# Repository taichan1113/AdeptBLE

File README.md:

# Excuse

This is alpha version of Ploopy Adept BLE modification.

All necessary files are here but they are still messy.

Document may not reach your satisfaction.

## electronics

Designed by KiCAD and produted by [JLCPCB](https://jlcpcb.com/)

Basically you need XIAO nRF52840 board, PMW3610 optical sensor, omron D2LS-21 mouse switch, 6-pin slide switch and battery.

Other parts are set as below.

## firmware

Here includes uf2 file built by zmk.

You can find the code [here](https://github.com/taichan1113/mouse-test/tree/main).

## housing

I designed like you only need bottom modified housing additionally.

Note that put the battery wire not to interfere both top and bottom housings.

And you need to cut battery switch so as not to interfere the desk surface.

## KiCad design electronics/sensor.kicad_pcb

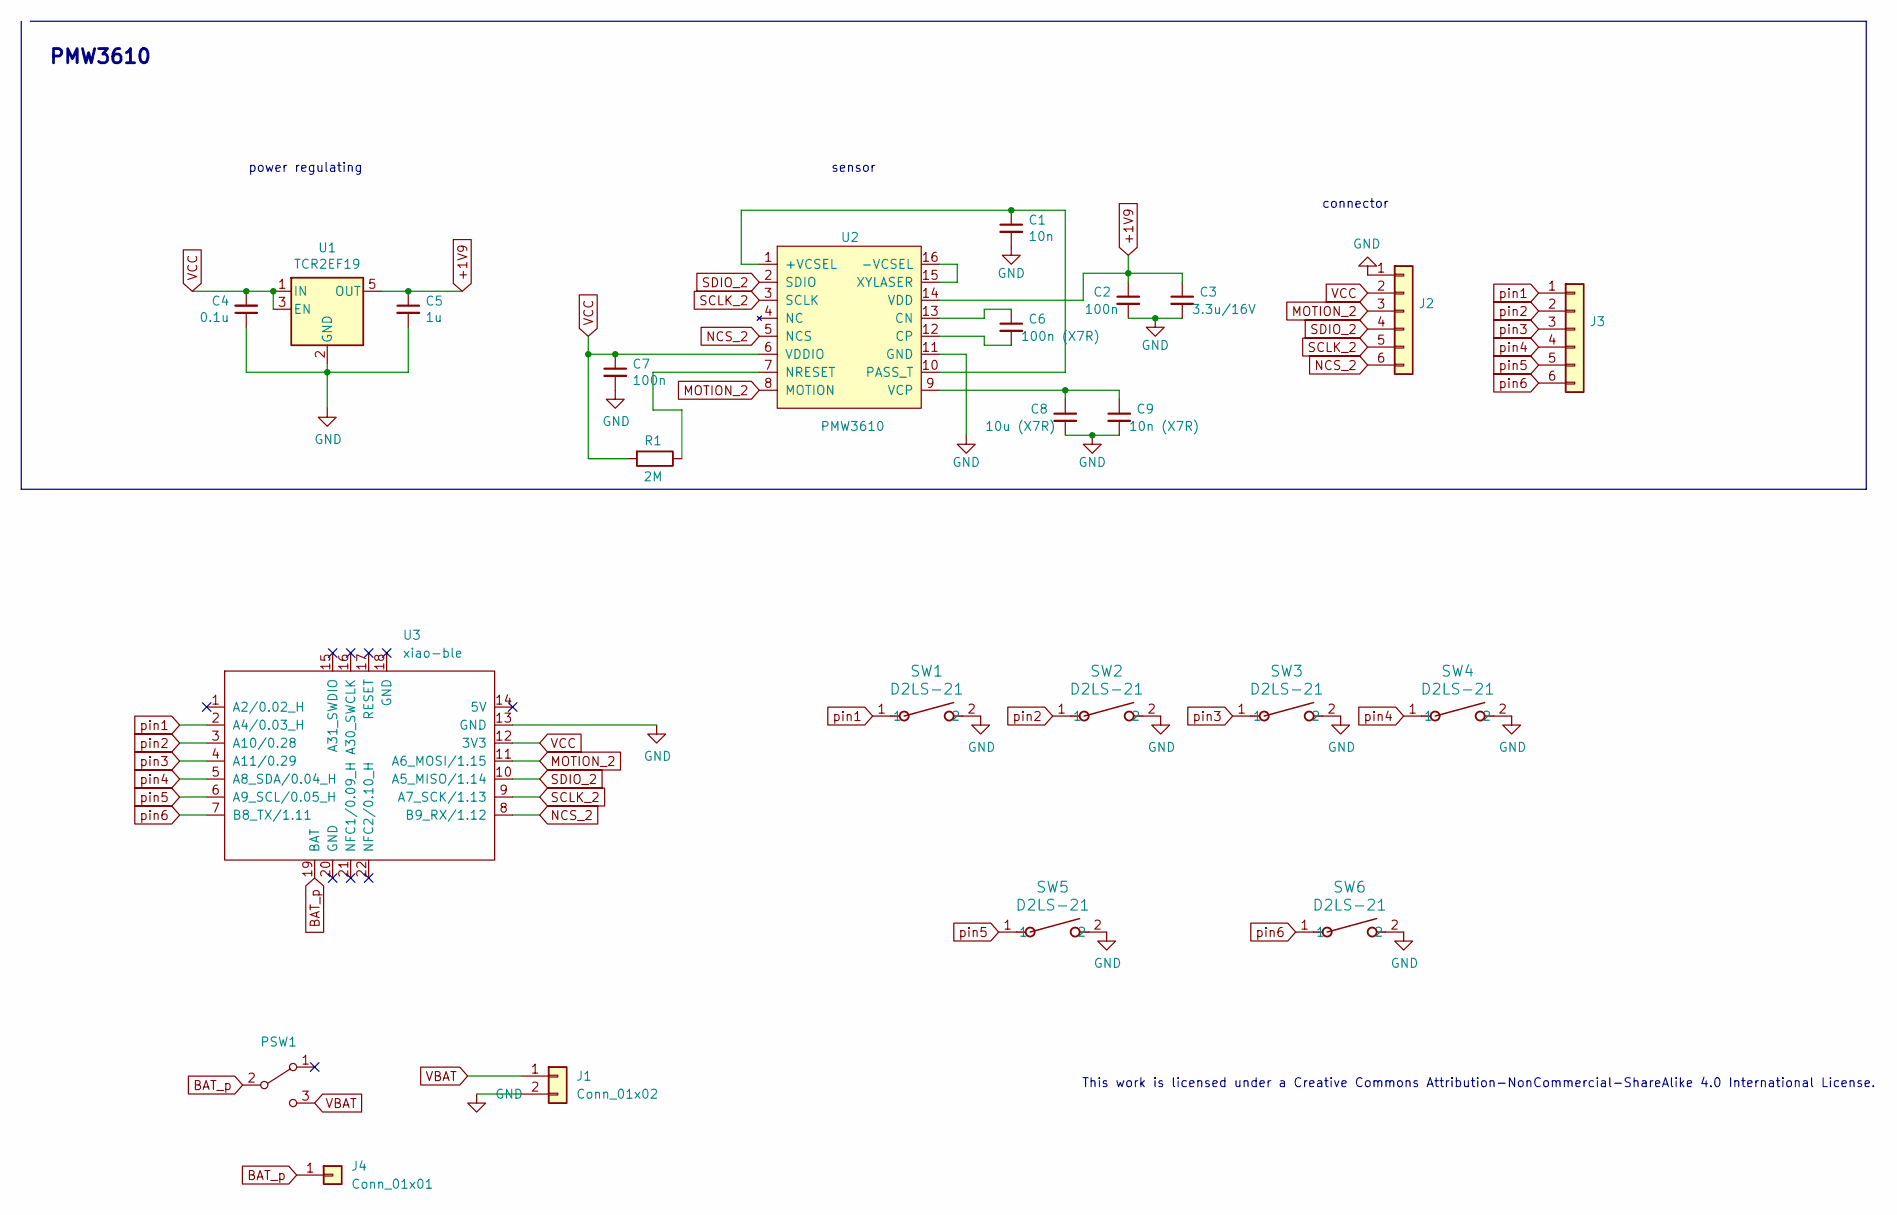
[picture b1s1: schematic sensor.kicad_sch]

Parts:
C1: 10n; C_0603_1608Metric; LCSC C19666
C2, C7: 100n; C_0603_1608Metric; LCSC C19666
C3: 3.3u/16V; C_0603_1608Metric; LCSC C19666
C4: 0.1u; C_0603_1608Metric; LCSC C14663
C5: 1u; C_0603_1608Metric; LCSC C15849
C6: 100n (X7R); C_0603_1608Metric; LCSC C19666
C8: 10u (X7R); C_0603_1608Metric; LCSC C19666
C9: 10n (X7R); C_0603_1608Metric; LCSC C19666
J1: Conn_01x02; Battery_2pin
J2, J3: Conn_01x06; PinHeader_1x06_P2.54mm_Vertical
J4: Conn_01x01; PinHeader_1x01_P2.54mm_Vertical
PSW1: SW_SPDT; TGSW_MSK-12D19
R1: 2M; R_0603_1608Metric
SW1, SW2, SW3, SW4, SW5, SW6: D2LS-21; SW_D2LS-11_2_OMR
U1: TCR2EF19; SOT-23-5; LCSC C146366
U2: PMW3610
U3: xiao-ble; xiao-ble-tht

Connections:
+1V9: C2.1, C3.1, C5.1, U1.5 (OUT), U2.14 (VDD)
BAT_p: J4.1, PSW1.2 (B), U3.19 (BAT)
GND: C1.2, C2.2, C3.2, C4.1, C5.2, C7.2, C8.2, C9.2, J1.2, J2.1, SW1.2, SW2.2, SW3.2, SW4.2, SW5.2, SW6.2, U1.2 (GND), U2.11 (GND), U3.13 (GND)
MOTION_2: J2.3, U2.8 (MOTION), U3.11 (A6_MOSI/1.15)
NCS_2: J2.6, U2.5 (NCS), U3.8 (B9_RX/1.12)
unnamed: C1.1, U2.1 (+VCSEL), U2.10 (PASS_T)
unnamed: U2.15 (XYLASER), U2.16 (-VCSEL)
unnamed: C6.1, U2.13 (CN)
unnamed: C6.2, U2.12 (CP)
unnamed: R1.1, U2.7 (NRESET)
unnamed: C8.1, C9.1, U2.9 (VCP)
SCLK_2: J2.5, U2.3 (SCLK), U3.9 (A7_SCK/1.13)
SDIO_2: J2.4, U2.2 (SDIO), U3.10 (A5_MISO/1.14)
VBAT: J1.1, PSW1.3 (C)
VCC: C4.2, C7.1, J2.2, R1.2, U1.1 (IN), U1.3 (EN), U2.6 (VDDIO), U3.12 (3V3)
pin1: J3.1, SW1.1, U3.2 (A4/0.03_H)
pin2: J3.2, SW2.1, U3.3 (A10/0.28)
pin3: J3.3, SW3.1, U3.4 (A11/0.29)
pin4: J3.4, SW4.1, U3.5 (A8_SDA/0.04_H)
pin5: J3.5, SW5.1, U3.6 (A9_SCL/0.05_H)
pin6: J3.6, SW6.1, U3.7 (B8_TX/1.11)

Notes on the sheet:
This work is licensed under a Creative Commons Attribution-NonCommercial-ShareAlike 4.0 International License.
sensor
PMW3610
power regulating
connector

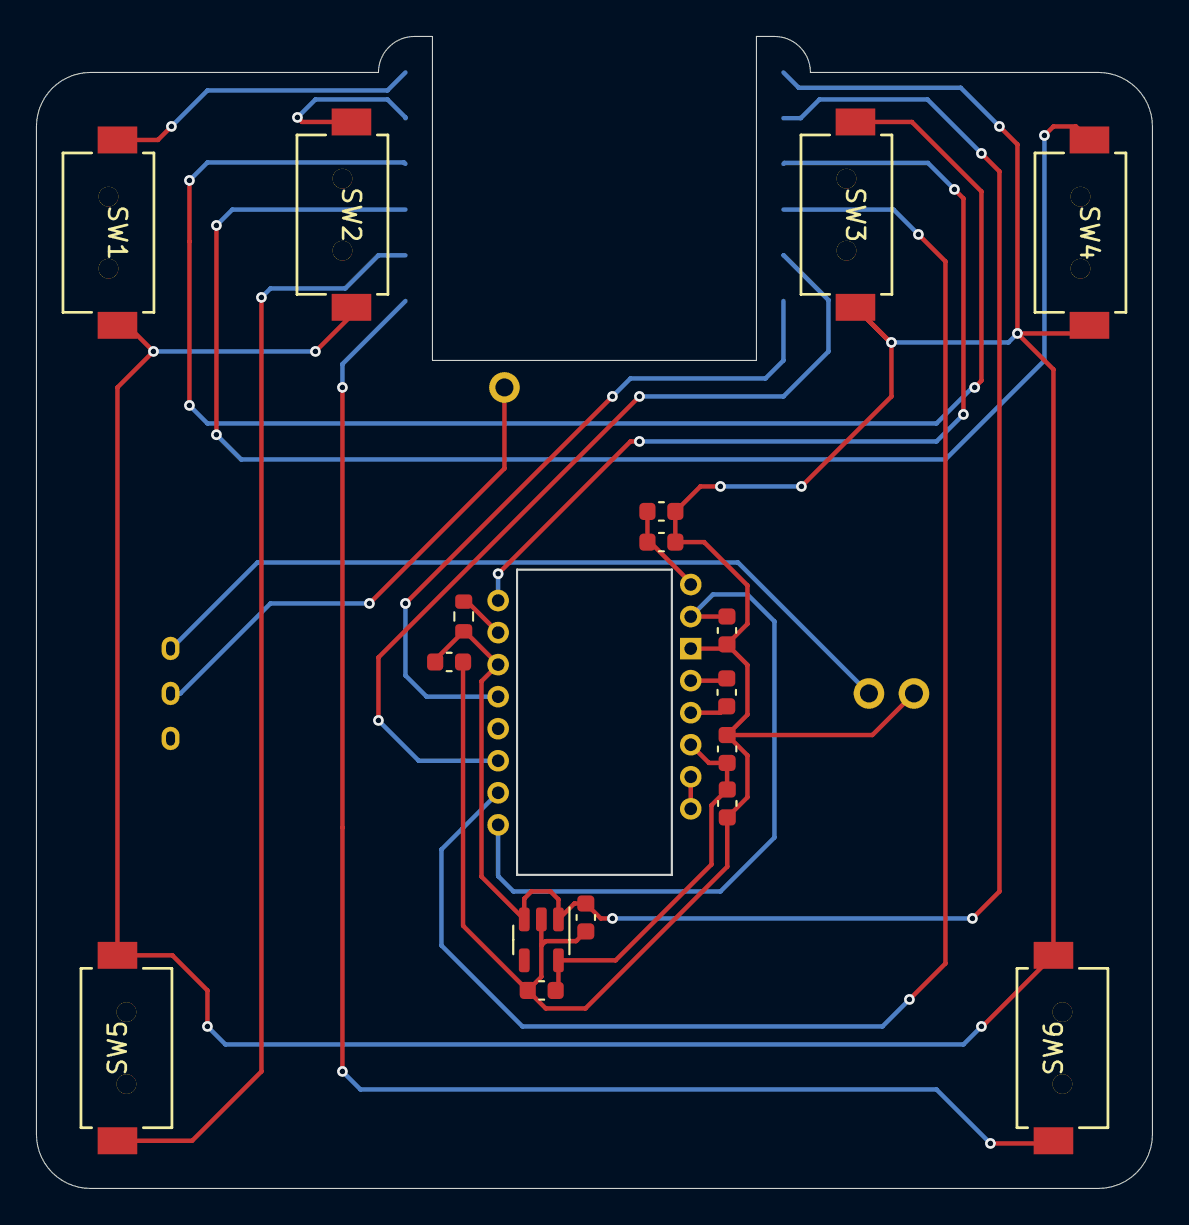
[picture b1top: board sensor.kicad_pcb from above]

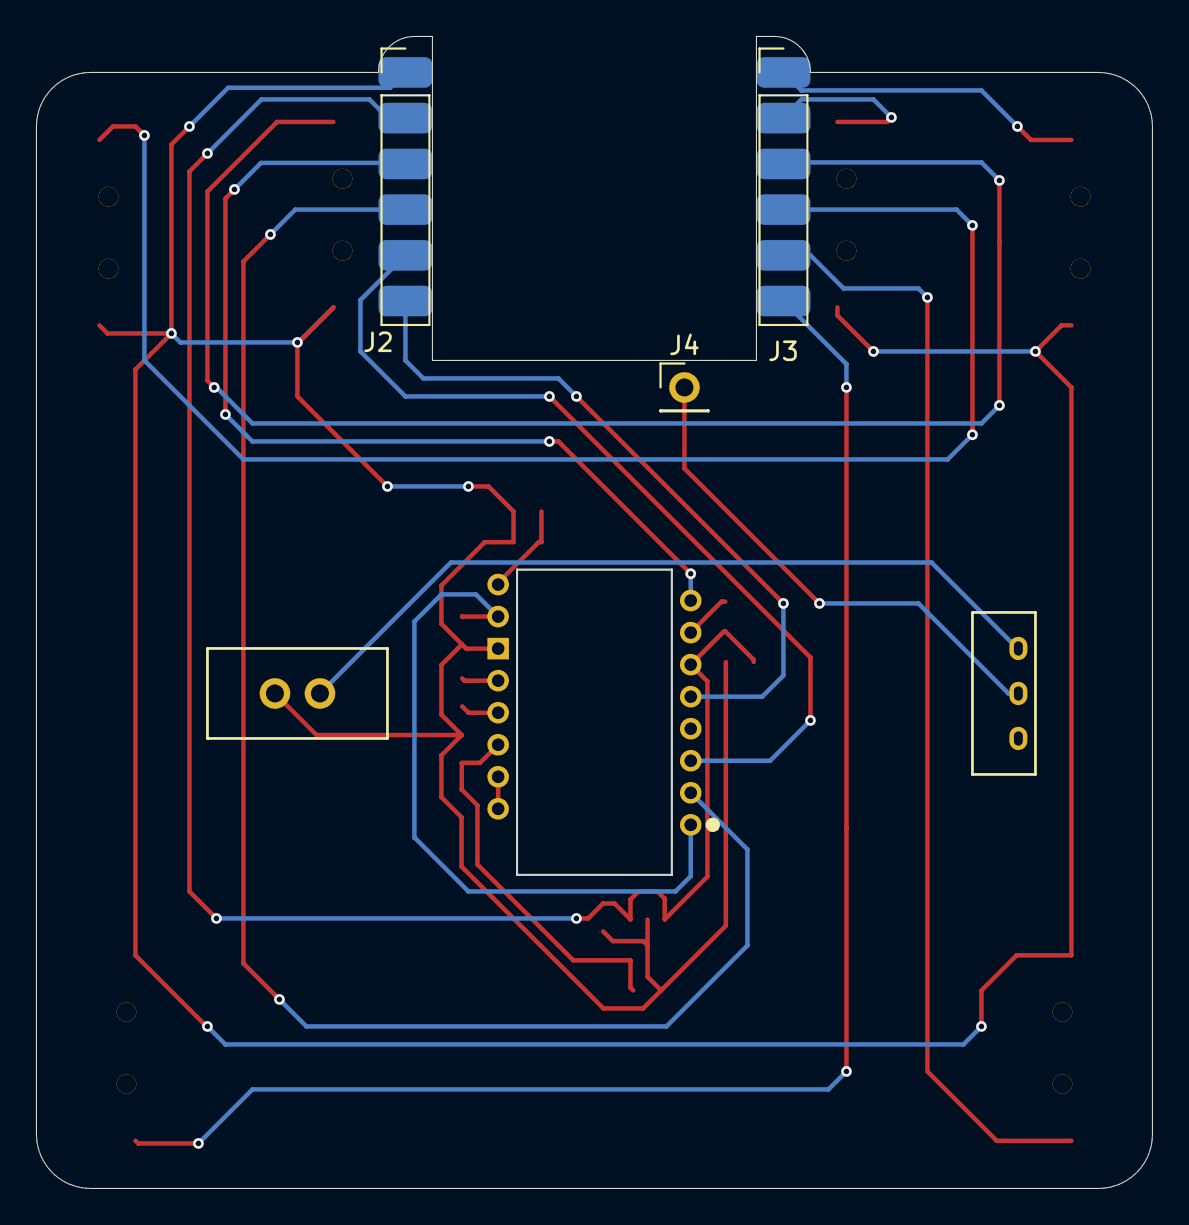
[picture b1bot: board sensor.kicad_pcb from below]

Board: 2 copper layers, 62.0 x 64.0 mm, 23 parts (6 on the bottom side), 21 nets.

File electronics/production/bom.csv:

Designator,Footprint,Quantity,Value,LCSC Part #
C1,0603,1,10n,C19666
"C2, C7",0603,2,100n,C19666
C3,0603,1,3.3u/16V,C19666
C4,0603,1,0.1u,C14663
C5,0603,1,1u,C15849
C6,0603,1, 100n (X7R),C19666
C8,0603,1, 10u (X7R),C19666
C9,0603,1, 10n (X7R),C19666
J1,Battery_2pin,1,Conn_01x02,
"J2, J3",PinHeader_1x06_P2.54mm_Vertical,2,Conn_01x06,
J4,PinHeader_1x01_P2.54mm_Vertical,1,Conn_01x01,
PSW1,TGSW_MSK-12D19,1,SW_SPDT,
R1,0603,1,2M,
"SW1, SW2, SW3, SW4, SW5, SW6",SW_D2LS-11_2_OMR,6,D2LS-21,
U1,SOT-23-5,1,TCR2EF19,C146366
U2,PMW3610,1,PMW3610,

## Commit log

2024-08-27 add firmware uf2
2024-08-27 add readme
2024-08-27 add lisence
2024-10-13 update: README
2025-04-01 bottom case step file uploaded
2025-04-02 submodule updated

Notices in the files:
electronics/sensor.kicad_sch:
Copyright Quentin Lebastard
